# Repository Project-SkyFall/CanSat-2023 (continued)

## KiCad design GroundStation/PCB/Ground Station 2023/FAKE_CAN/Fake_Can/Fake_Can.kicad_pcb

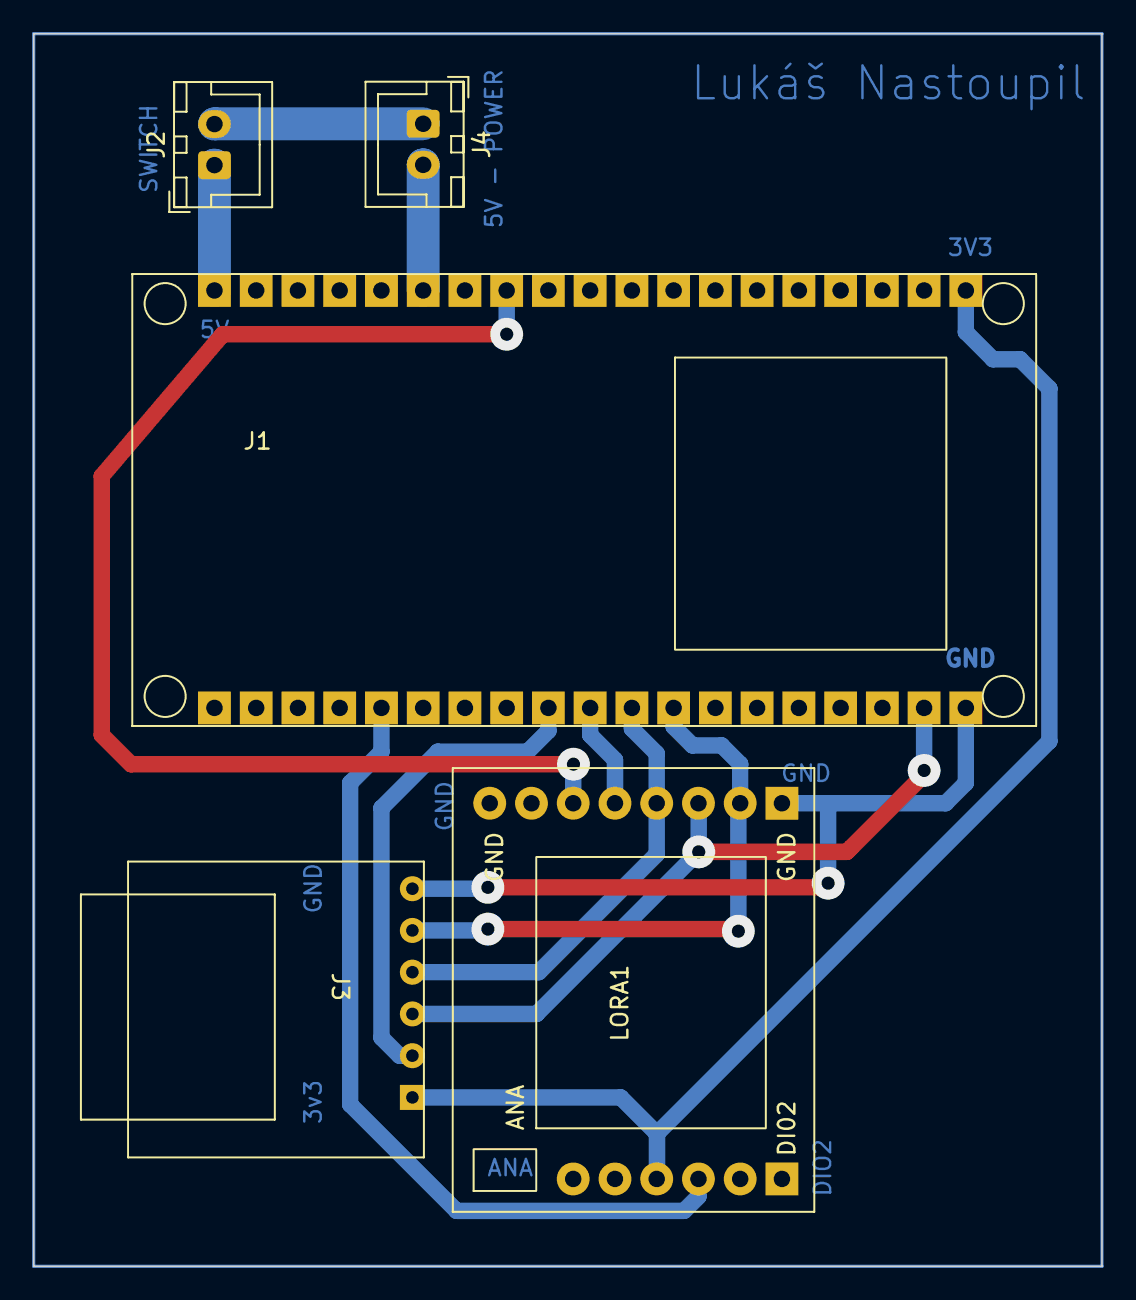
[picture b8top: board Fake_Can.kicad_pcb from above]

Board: 2 copper layers, 65.0 x 75.0 mm, 5 parts (0 on the bottom side), 11 nets.

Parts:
J1: ESP_32
J2: SWITCH; JST_XH_B2B-XH-A_1x02_P2.50mm_Vertical
J3: SD_card; SD_Card
J4: POWER; JST_XH_B2B-XH-A_1x02_P2.50mm_Vertical
LORA1: LORA; Lora deska

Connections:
+3V3: J1.20, J3.6, LORA1.5
CS: J1.9, J3.5
DI00: J1.5, LORA1.6
GNDD: J1.13, J1.19, J1.33, J3.1, J4.2, LORA1.9, LORA1.16
MISO: J1.12, J3.2, LORA1.10
MOSI: J1.18, J3.4, LORA1.11
NSS: J1.10, LORA1.13
unnamed: J1.38, J2.1
unnamed: J2.2, J4.1
RESET: J1.31, LORA1.14
SCK: J1.11, J3.3, LORA1.12

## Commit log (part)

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2022-12-22 Initial request
2022-12-22 Initial push
2022-12-23 Modified gitignore
2022-12-23 Modifying README.md
2022-12-25 Rerouted J2 paths
2022-12-26 Added CanSat local library
2022-12-26 Placed capacitor, no DRC errors
2022-12-26 Renumbered Control Unit sheets
2022-12-26 Changed packages 0402 -> 0804
2022-12-27 Fixed clipped silkscreen
2022-12-27 Renumbered references - power unit
2022-12-27 Changed RX, TX leds
2022-12-29 Changed order of pins - J2
2023-01-02 Hello there
2023-01-02 Revert "Hello there"
2023-01-02 Složka vytvořena
2023-01-02 Zkouška sirén
2023-01-02 Spraveno
2023-01-02 Deleted README.md
2023-01-02 Edited README.md
2023-01-03 Complete layout - zero error - Power Unit
2023-01-03 Added 3D models folder
2023-01-03 Add side PCBs
2023-01-03 updated Side PCBs
2023-01-03 updated Side PCBs No.2
2023-01-03 Added RFM96W datasheet
2023-01-03 update something, but i dont remember what
2023-01-06 Edge cuts v0.1
2023-01-06 Side Units - blank project
2023-01-07 Re-organised directories
2023-01-07 add edge_cuts_DXFs
2023-01-07 WIP commit
2023-01-07 trying to fix fucking kiCad
2023-01-07 fuck your mum kicad
2023-01-07 kicad fock you last time
2023-01-07 New edge cuts
2023-01-08 Created STEP models
2023-01-10 changed PCBs DXFs
2023-01-10 New STEP models
2023-01-12 update some things
2023-01-12 update CU edge cuts
2023-01-12 DXF logo
2023-01-12 final final edge cuts
2023-01-12 PCB FINAL?
2023-01-12 Program
2023-01-13 PCB_Final
2023-01-15 Modified Logo_vFINAL.dxf
2023-01-15 Updated 3D exports
2023-01-17 Production folder
2023-01-17 Production files
2023-01-17 Resolving gitignore
2023-01-17 Updated gitignore (removed Side Unit-backup, *.kicad_prl
2023-01-17 LoRa step
2023-01-17 Working version of PCBs (before final)
2023-01-17 3D export
2023-01-17 PCB before last check
2023-01-17 Added component values
2023-01-17 Realignmented Pinheaders
2023-01-17 New version of STEPs
2023-01-17 worked
2023-01-18 18.1.2023 - final
2023-01-19 Add LoRa breakup board
2023-01-21 PCB FINAL snad
2023-01-24 Created gitignore
2023-01-24 Final PCBs 24.1.2023
2023-01-29 Huge amount of changes, WIP
2023-01-29 BME280 - created constructor
2023-01-30 Added DS18B20 sensor
2023-01-30 NeoPixel default template
2023-01-30 Get data delay change
2023-01-30 Neo clear in setup
2023-02-01 raspi
2023-02-02 RASPIv3
2023-02-02 LoraProgram_update
2023-02-02 Lora_update
2023-02-07 Renewed libdeps - SDFat + BNO055 + NeoPixel
2023-02-07 Optimized verbose print options
2023-02-07 Added fiducial markers
2023-02-07 Renumbered parts
2023-02-07 Renewed folder path
2023-02-07 Moved to separated branch
2023-02-07 Transfer from another branch
2023-02-10 Removed server folder from workspace
2023-02-10 Fixed SPI CS syntax error - removed unused object
2023-02-13 MyCO2 template
2023-02-13 LoRa callback + own private methods + own constructor + onTxDone callback
2023-02-16 Created MyLora::dumpRegisters -modified former dumpRegisters to print in binary
2023-02-16 Lora sends before semaphore give
2023-02-18 Created own endPacket method + New method was necessary, because of private declaration of base LoRa class
2023-02-18 Lora ISR moved to FreeRTOS task
2023-02-18 SD repeatable mount + SDcard tries to mount 5 times before aborting
2023-02-18 LoRa register definitions
2023-02-18 Removed _bus
2023-02-18 WiFi Server setup messages + modifie verbose setup messages to match standart
2023-02-18 Removed duplicate files - .gitignore -> moved to nested folder
2023-02-18 Server and Wifi + added default FALSE verbose option in `server.setup()` + created MyWiFi constructor + `softAP()` now takes privated variables + low TX power -> 20dBm + `MyServer::mode()` + `MyServe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
2023-02-18 Cosmetic changes
2023-02-18 Created myTask resume + tries to resume task in try{} block (hopefully will resolve crashes)
2023-02-18 ISR LoRa handle
2023-02-18 RunServer
2023-02-18 Modified .code.workspace
2023-02-18 Created control task
2023-02-22 nothing
2023-02-25 Resolving wrong hiearchy
2023-02-25 Created status enums
2023-02-25 Mode enumeration
2023-02-25 PrintResult print style ~ changed - for =
2023-02-26 26.02.2023 construction
2023-03-22 Final v1
2023-03-22 Main update
2023-03-25 Test
2023-03-25 update all const
2023-03-25 Fixed SCD41 returned fail in setup
2023-03-25 renamed getData_task to getData_handle
2023-03-25 Task notify system + GPS get data notify + DS18 get data notify [fix needed]
2023-03-25 RTC constructor
2023-03-27 asddada
2023-03-27 dasd
2023-03-27 Vizu update
2023-03-27 GPS return data in usable format
2023-03-27 New background
2023-03-27 Before IMU side switch
2023-03-28 updt
2023-03-31 Main update (RT)
2023-04-06 funkční
2023-04-07 070423
2023-04-14 Main update (pozice a velikost kamerky)
2023-04-14 Test = False
2023-04-16 GUI phase II
2023-04-16 Kamera final
2023-04-18 GUI 2 final
2023-04-18 GUI 3
2023-04-19 Moving new files
2023-04-19 Adding styles
2023-04-20 Big commit +idk really, just lot of changes
2023-04-20 Navrhnuti orezu
2023-04-21 GUI III
2023-04-23 Updating functionality
2023-04-24 GUI final
2023-04-25 Blue
2023-04-26 final
2023-04-26 skoro final
2023-04-26 uplne final
2023-04-26 update radiany
2023-04-26 update error
2023-04-26 current
2023-04-26 current plot
2023-04-26 update2
2023-04-26 model update
2023-04-26 Model
2023-04-26 update fig error
2023-04-26 camera update
2023-04-26 Cam dORa11
2023-04-26 new back
2023-04-26 Text pos
2023-04-26 time2
2023-04-26 co2 ruc
2023-04-26 time2 update
2023-04-27 Fungující GS(verze v den finále v 4:45)
2023-04-27 Stable version - preFinal 1
2023-04-27 Intensity
2023-04-27 adata
2023-04-29 update all
2023-04-29 add photos
2023-05-06 National Final 2023
2023-05-06 National Final
2023-05-06 Ready to everything
2023-05-12 Renewed path
2023-06-01 Initial version of Smart Audio [UNTESTED]
2023-06-04 Fixed warnings
2023-06-07 Debug
2023-06-07 Untest
2023-06-09 National Finals documentation
2023-06-18 Window resize
2023-06-18 Trajectory
2023-06-21 SD card rework ~Files now dont close¨ ~No crashes -Unused tasks
2023-06-21 SD rework #2
2023-06-24 Test 2
2023-06-24 Test TC 24.6
2023-06-24 Frame and socketio
2023-07-05 update up to date
2023-07-06 photos1
2023-07-06 photos2
2023-07-06 photosFinal
2023-10-21 Added Final report
2023-10-21 Added National Final's diploma
2023-10-21 Added team profile pictures
2023-10-21 New path to Europien Finale photos #1
2023-10-21 New path to Europien Finale photos #2
2024-03-22 Change path #1
2024-03-22 Changed path #2
2024-03-22 Revert "Change path to pictures"
2026-06-02 Fix gitignore: untrack backups, fix .bak pattern
2026-06-02 Cleaning
2026-06-02 add pcb_design
2026-06-02 Ground station (#22)
    * asddada
    * dasd
    * Main update
    * Fungující GS(verze v den finále v 4:45)
    * adata
    ---------
2026-06-02 Visualization (#23)
    * Debug
    * Untest
    * Window resize
    * Trajectory
    * Untest
    * Delete test data
2026-06-03 removed pictures
2026-06-03 removed pictures (#24)
2026-06-03 add construction
2026-06-03 updated construction
2026-06-03 removed documentation
2026-06-03 Web (#25)
    * First commit
    * Modifying README.md
    ---------
2026-06-03 Cleanup (#26)
    * First commit
    * Modifying README.md
    * Složka vytvořena
    * Zkouška sirén
    * Spraveno
    * Update README.md
2026-06-03 Can sat web (#27)
    * Transfer from another branch
    * Moving new files
    * Adding styles
    * Updating functionality
    ---------
